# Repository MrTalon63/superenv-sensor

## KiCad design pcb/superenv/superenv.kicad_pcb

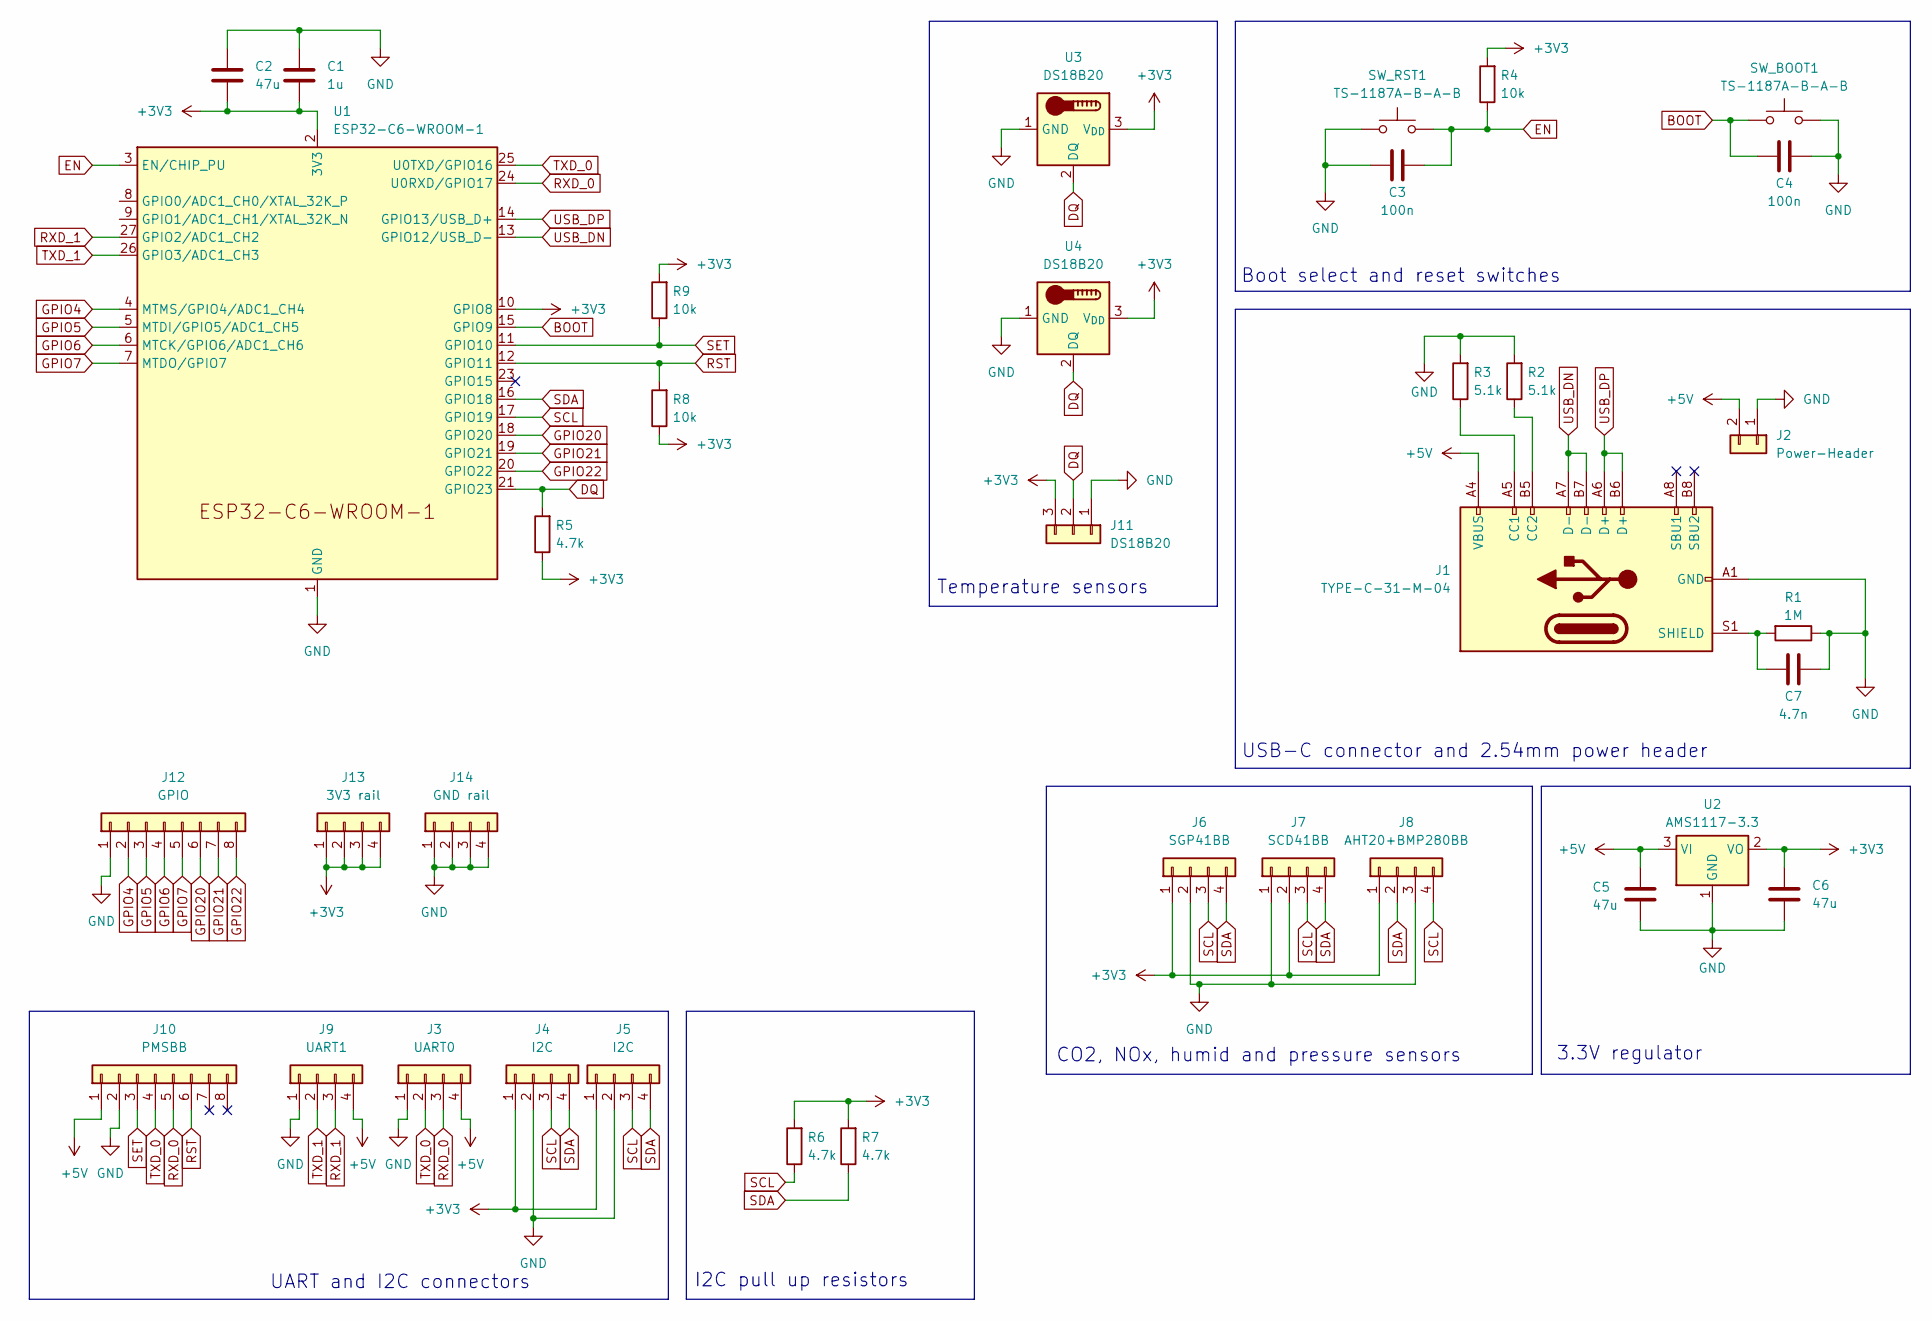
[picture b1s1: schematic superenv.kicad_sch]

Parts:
C1: 1u; C_0603_1608Metric
C2, C5, C6: 47u; C_0805_2012Metric
C3, C4: 100n; C_0603_1608Metric
C7: 4.7n; C_0603_1608Metric
J1: TYPE-C-31-M-04; USB_C_Receptacle_HRO_TYPE-C-31-M-12
J2: Power-Header; PinHeader_1x02_P2.54mm_Vertical
J3: UART0; PinHeader_1x04_P2.54mm_Vertical
J4, J5: I2C; PinHeader_1x04_P2.54mm_Vertical
J6: SGP41BB; PinHeader_1x04_P2.54mm_Vertical
J7: SCD41BB; PinHeader_1x04_P2.54mm_Vertical
J8: AHT20+BMP280BB; PinHeader_1x04_P2.54mm_Vertical
J9: UART1; PinHeader_1x04_P2.54mm_Vertical
J10: PMSBB; JST_GH_BM08B-GHS-TBT_1x08-1MP_P1.25mm_Vertical
J11: DS18B20; PinHeader_1x03_P2.54mm_Vertical
J12: GPIO; PinHeader_1x08_P2.54mm_Vertical
J13: 3V3 rail; PinHeader_1x04_P2.54mm_Vertical
J14: GND rail; PinHeader_1x04_P2.54mm_Vertical
R1: 1M; R_0603_1608Metric
R2, R3: 5.1k; R_0603_1608Metric
R4, R8, R9: 10k; R_0603_1608Metric
R5, R6, R7: 4.7k; R_0603_1608Metric
SW_BOOT1: TS-1187A-B-A-B; SW_Push_1P1T_XKB_TS-1187A
SW_RST1: TS-1187A-B-A-B; SW_Push_1P1T_XKB_TS-1187A
U1: ESP32-C6-WROOM-1
U2: AMS1117-3.3; SOT-223-3_TabPin2
U3, U4: DS18B20; TO-92_Inline

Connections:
+3V3: C1.2, C2.2, C6.1, J4.1, J5.1, J6.1, J7.2, J8.1, J11.3, J13.1, J13.2, J13.3, J13.4, R4.2, R5.1, R6.2, R7.2, R8.1, R9.2, U1.2 (3V3), U1.10 (GPIO8), U2.2 (VO), U3.3 (V_{DD}), U4.3 (V_{DD})
+5V: C5.1, J1.A4 (VBUS), J1.A9 (VBUS), J1.B4 (VBUS), J1.B9 (VBUS), J2.2, J3.4, J9.4, J10.1, U2.3 (VI)
BOOT: C4.1, SW_BOOT1.1, U1.15 (GPIO9)
DQ: J11.2, R5.2, U1.21 (GPIO23), U3.2 (DQ), U4.2 (DQ)
EN: C3.2, R4.1, SW_RST1.2, U1.3 (EN/CHIP_PU)
GND: C1.1, C2.1, C3.1, C4.2, C5.2, C6.2, C7.2, J1.A1 (GND), J1.A12 (GND), J1.B1 (GND), J1.B12 (GND), J2.1, J3.1, J4.2, J5.2, J6.2, J7.1, J8.3, J9.1, J10.2, J11.1, J12.1, J14.1, J14.2, J14.3, J14.4, R1.1, R2.2, R3.2, SW_BOOT1.2, SW_RST1.1, U1.1 (GND), U1.28 (GND), U1.29 (GND), U2.1 (GND), U3.1 (GND), U4.1 (GND)
GPIO4: J12.2, U1.4 (MTMS/GPIO4/ADC1_CH4)
GPIO5: J12.3, U1.5 (MTDI/GPIO5/ADC1_CH5)
GPIO6: J12.4, U1.6 (MTCK/GPIO6/ADC1_CH6)
GPIO7: J12.5, U1.7 (MTDO/GPIO7)
GPIO20: J12.6, U1.18 (GPIO20)
GPIO21: J12.7, U1.19 (GPIO21)
GPIO22: J12.8, U1.20 (GPIO22)
unnamed: J1.A5 (CC1), R3.1
unnamed: J1.B5 (CC2), R2.1
unnamed: C7.1, J1.S1 (SHIELD), R1.2
RST: J10.6, R8.2, U1.12 (GPIO11)
RXD_0: J3.3, J10.5, U1.24 (U0RXD/GPIO17)
RXD_1: J9.3, U1.27 (GPIO2/ADC1_CH2)
SCL: J4.3, J5.3, J6.3, J7.3, J8.4, R6.1, U1.17 (GPIO19)
SDA: J4.4, J5.4, J6.4, J7.4, J8.2, R7.1, U1.16 (GPIO18)
SET: J10.3, R9.1, U1.11 (GPIO10)
TXD_0: J3.2, J10.4, U1.25 (U0TXD/GPIO16)
TXD_1: J9.2, U1.26 (GPIO3/ADC1_CH3)
USB_DN: J1.A7 (D-), J1.B7 (D-), U1.13 (GPIO12/USB_D-)
USB_DP: J1.A6 (D+), J1.B6 (D+), U1.14 (GPIO13/USB_D+)

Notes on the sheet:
USB-C connector and 2.54mm power header
I2C pull up resistors
3.3V regulator
CO2, NOx, humid and pressure sensors
UART and I2C connectors
Boot select and reset switches
Temperature sensors

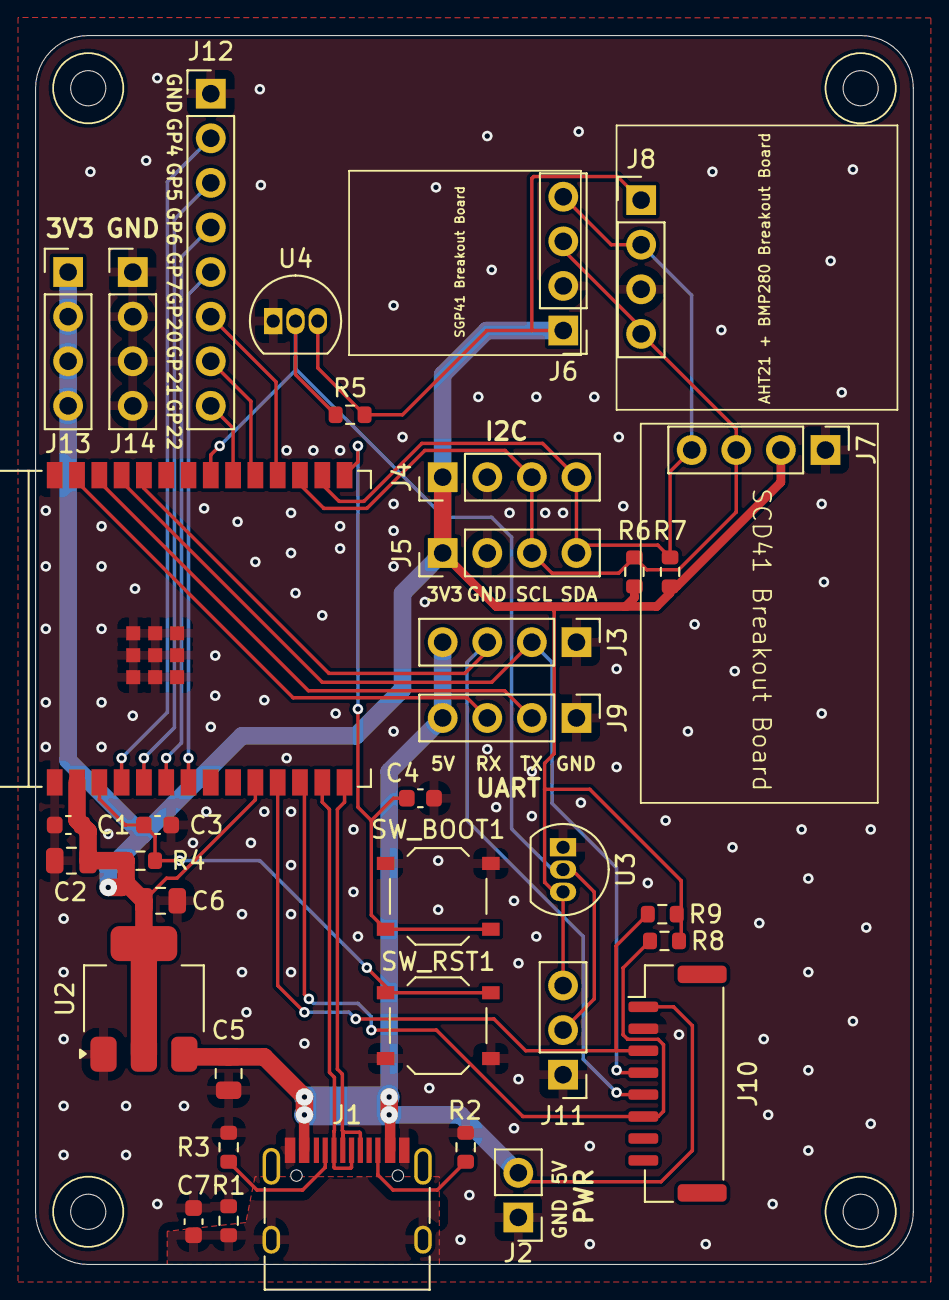
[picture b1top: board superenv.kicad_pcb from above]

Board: 2 copper layers, 50.0 x 70.0 mm, 36 parts (0 on the bottom side), 26 nets.

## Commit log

2025-03-11 Add I2C pull ups
2025-03-13 Add I2C sensors
2025-03-13 Add stuff
2025-03-15 test commit signing
2025-03-18 Update gitignore and finish v1
